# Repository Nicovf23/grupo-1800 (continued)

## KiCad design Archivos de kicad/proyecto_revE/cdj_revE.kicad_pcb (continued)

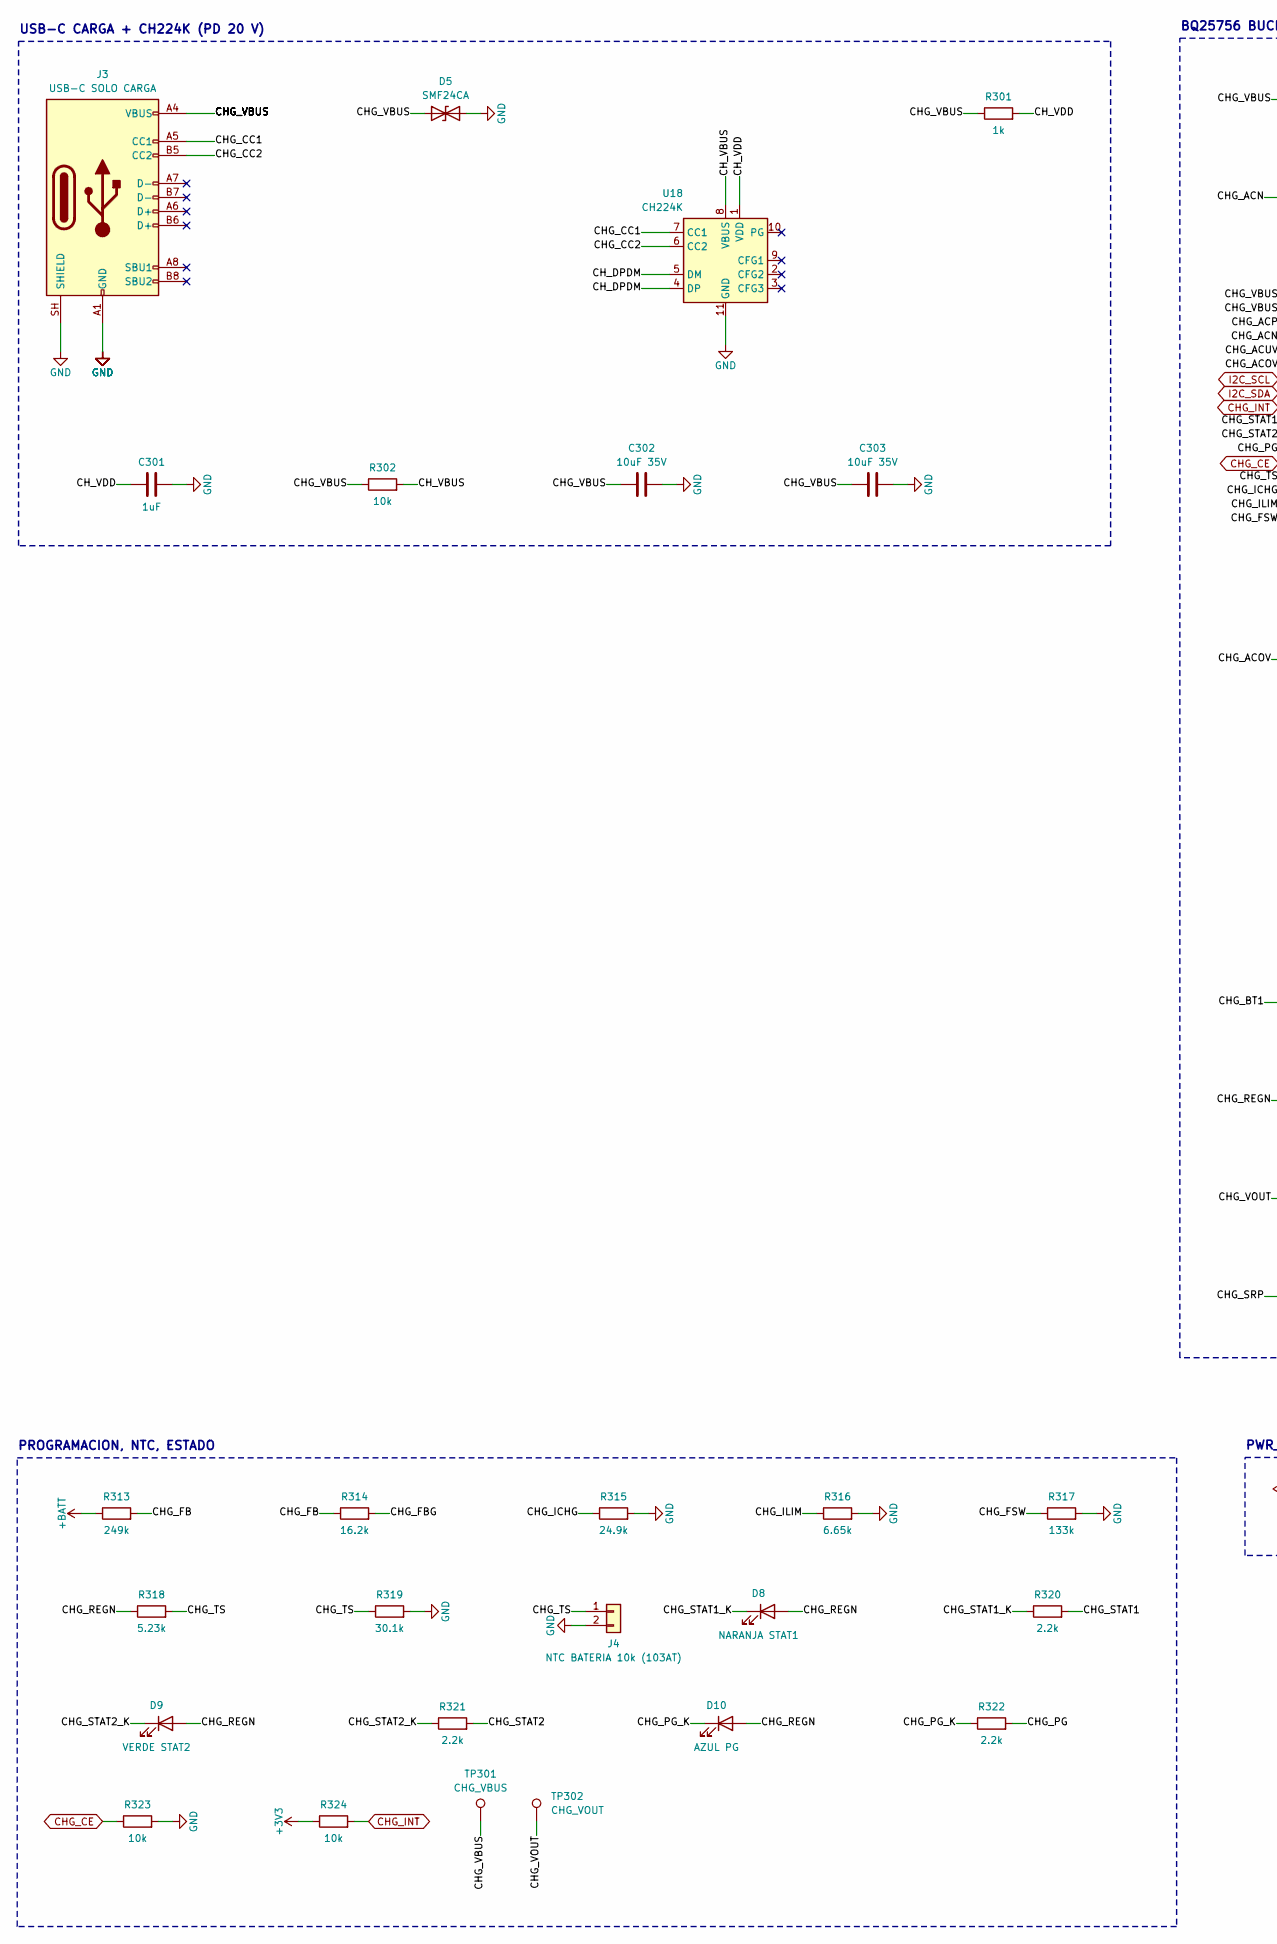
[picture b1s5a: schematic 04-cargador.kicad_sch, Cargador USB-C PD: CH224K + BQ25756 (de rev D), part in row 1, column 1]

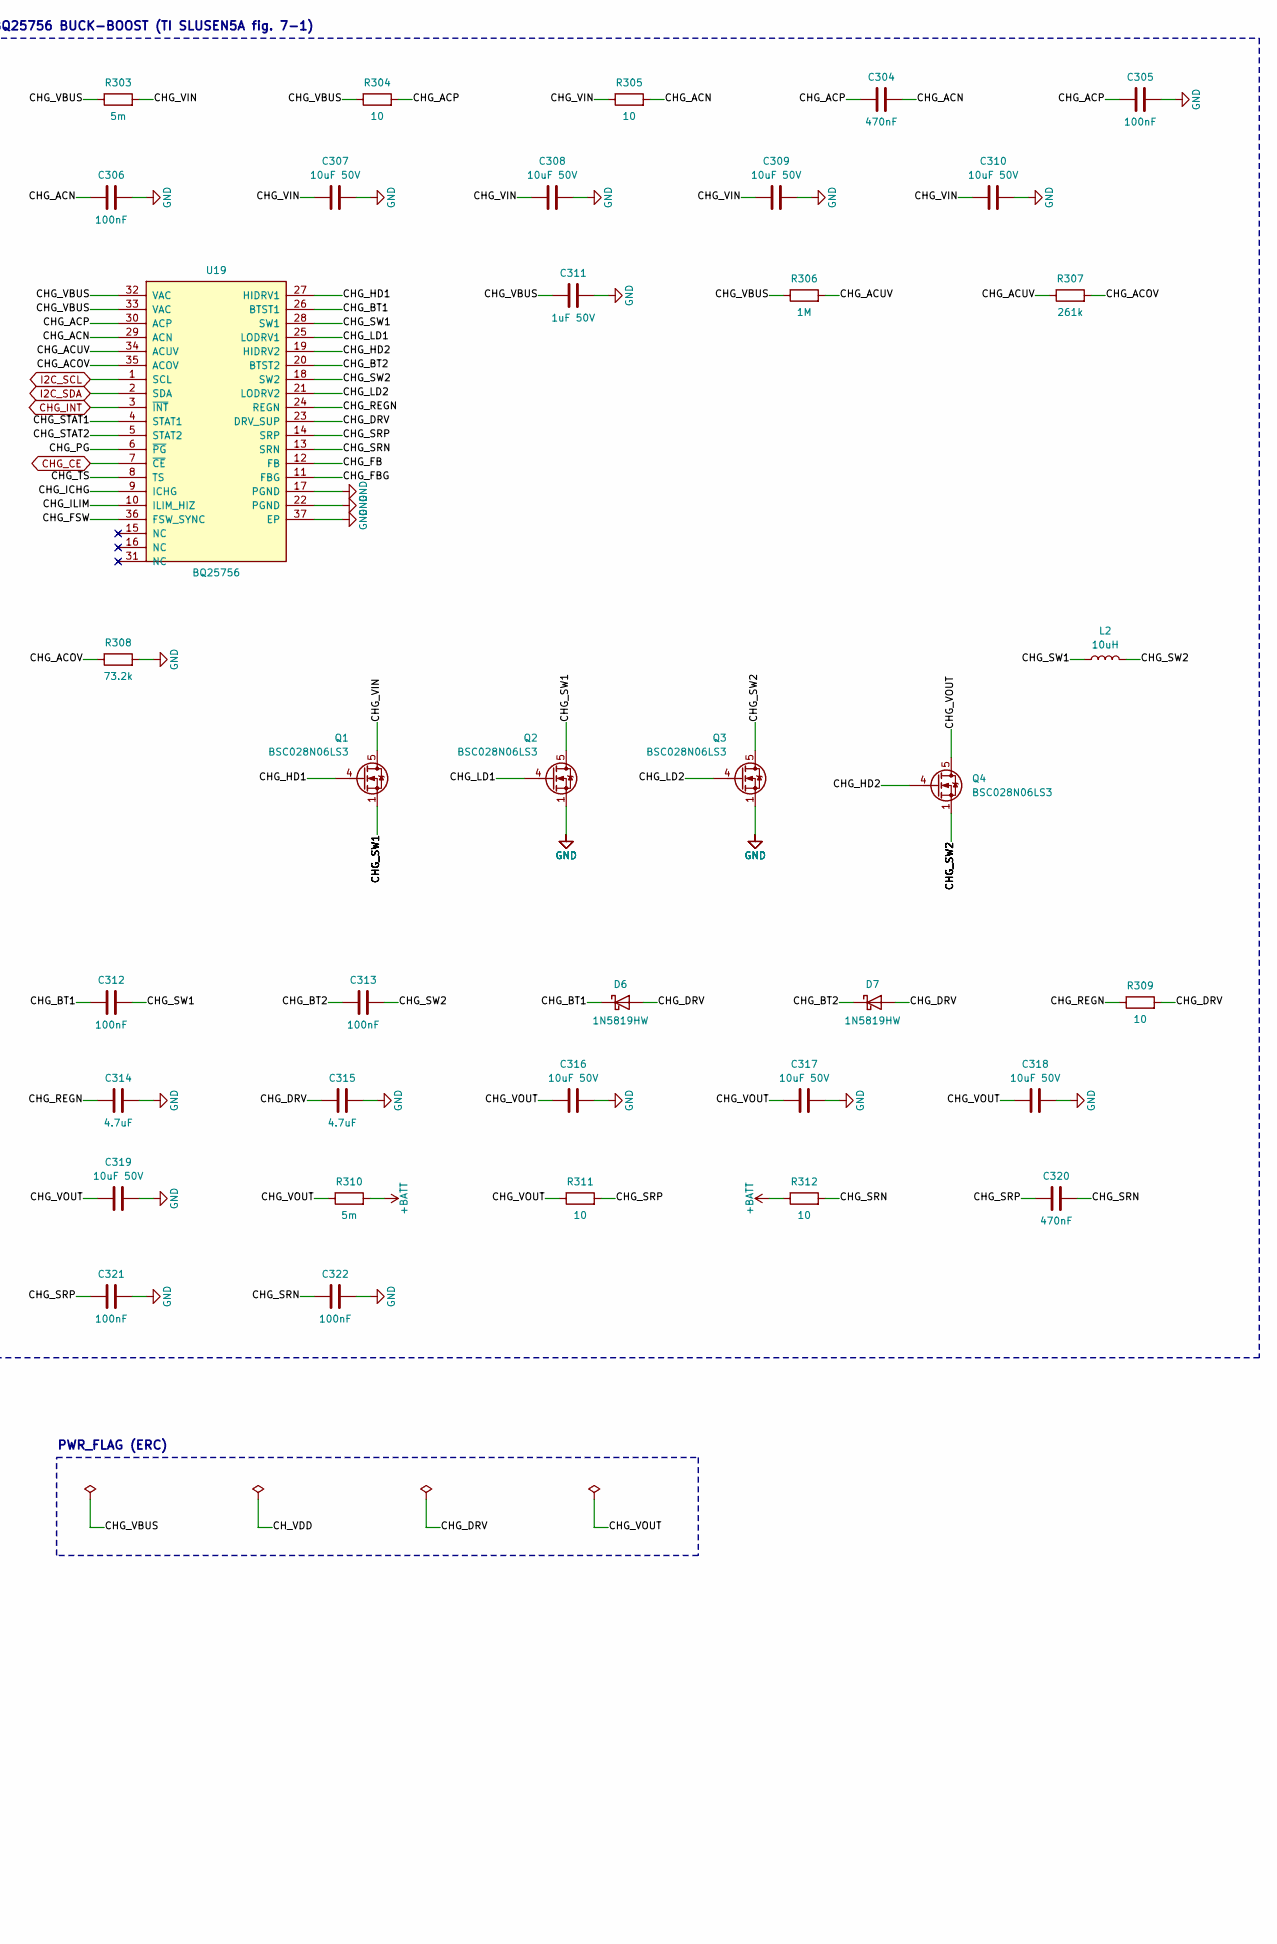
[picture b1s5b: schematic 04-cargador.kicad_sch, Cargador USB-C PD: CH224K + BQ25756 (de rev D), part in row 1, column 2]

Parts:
C301: 1uF; C_0603_1608Metric; MPN X7R 0603 25 V
C302, C303: 10uF 35V; C_1206_3216Metric; MPN X5R 1206 35 V
C304, C320: 470nF; C_0603_1608Metric; MPN X7R 0603 50 V
C305, C306, C321, C322: 100nF; C_0603_1608Metric; MPN X7R 0603 50 V
C307, C308, C309, C310, C316, C317, C318, C319: 10uF 50V; C_1206_3216Metric; MPN X5R 1206 50 V
C311: 1uF 50V; C_0603_1608Metric; MPN X7R 0603 50 V (VAC)
C312: 100nF; C_0603_1608Metric; MPN X7R 0603 25 V (bootstrap 1)
C313: 100nF; C_0603_1608Metric; MPN X7R 0603 25 V (bootstrap 2)
C314, C315: 4.7uF; C_0805_2012Metric; MPN X7R 0805 16 V
D5: SMF24CA; D_SOD-123F; MPN Littelfuse SMF24CA (profesor; PD 20 V <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
D6, D7: 1N5819HW; D_SOD-123; MPN Diodes 1N5819HW-7-F (profesor)
D8: NARANJA STAT1; LED_0603_1608Metric; MPN LED 0603
D9: VERDE STAT2; LED_0603_1608Metric; MPN LED 0603
D10: AZUL PG; LED_0603_1608Metric; MPN LED 0603
J3: USB-C SOLO CARGA; USB_C_Receptacle_HRO_TYPE-C-31-M-12; MPN HRO TYPE-C-31-M-12
J4: NTC BATERIA 10k (103AT); JST_PH_B2B-PH-K_1x02_P2.00mm_Vertical; MPN JST B2B-PH-K-S
L2: 10uH; L_Vishay_IHLP-4040; MPN Vishay IHLP4040DZER100M5A (10 uH, 6.5 A)
Q1, Q2, Q3, Q4: BSC028N06LS3; TDSON-8-1; MPN Infineon BSC028N06LS3 (60 V, 2.8 mOhm)
R301: 1k; R_0603_1608Metric; MPN 1 % 0603
R302, R324: 10k; R_0603_1608Metric; MPN 1 % 0603
R303: 5m; R_1206_3216Metric; MPN Shunt 5 mOhm 1206 1 W (RAC_SNS)
R304, R305, R309, R311, R312: 10; R_0603_1608Metric; MPN 1 % 0603
R306: 1M; R_0603_1608Metric; MPN 1 % 0603
R307: 261k; R_0603_1608Metric; MPN 1 % 0603
R308: 73.2k; R_0603_1608Metric; MPN 1 % 0603
R310: 5m; R_1206_3216Metric; MPN Shunt 5 mOhm 1206 1 W (RBAT_SNS)
R313: 249k; R_0603_1608Metric; MPN 1 % 0603 (FB: 25.14 V)
R314: 16.2k; R_0603_1608Metric; MPN 1 % 0603
R315: 24.9k; R_0603_1608Metric; MPN 1 % 0603 (ICHG 2.0 A)
R316: 6.65k; R_0603_1608Metric; MPN 1 % 0603 (ILIM 3.0 A)
R317: 133k; R_0603_1608Metric; MPN 1 % 0603 (250 kHz)
R318: 5.23k; R_0603_1608Metric; MPN 1 % 0603
R319: 30.1k; R_0603_1608Metric; MPN 1 % 0603
R320, R321, R322: 2.2k; R_0603_1608Metric; MPN 1 % 0603
R323: 10k; R_0603_1608Metric; MPN 1 % 0603 (carga habilitada sin ESP32)
TP301: CHG_VBUS; TestPoint_Pad_D1.5mm; MPN Pad de prueba
TP302: CHG_VOUT; TestPoint_Pad_D1.5mm; MPN Pad de prueba
U18: CH224K; SSOP-10-1EP_3.9x4.9mm_P1mm_EP2.1x3.3mm; MPN WCH CH224K
U19: BQ25756; QFN-36-1EP_5x6mm_P0.5mm_EP3.6x4.6mm; MPN TI BQ25756RRVR

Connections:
/Cargador USB-C PD: CH224K + BQ25756 (de rev D)/CHG_ACN: C304.2, C306.1, R305.2, U19.29 (ACN)
/Cargador USB-C PD: CH224K + BQ25756 (de rev D)/CHG_ACOV: R307.2, R308.1, U19.35 (ACOV)
/Cargador USB-C PD: CH224K + BQ25756 (de rev D)/CHG_ACP: C304.1, C305.1, R304.2, U19.30 (ACP)
/Cargador USB-C PD: CH224K + BQ25756 (de rev D)/CHG_ACUV: R306.2, R307.1, U19.34 (ACUV)
/Cargador USB-C PD: CH224K + BQ25756 (de rev D)/CHG_BT1: C312.1, D6.1 (K), U19.26 (BTST1)
/Cargador USB-C PD: CH224K + BQ25756 (de rev D)/CHG_BT2: C313.1, D7.1 (K), U19.20 (BTST2)
/Cargador USB-C PD: CH224K + BQ25756 (de rev D)/CHG_CC1: J3.A5 (CC1), U18.7 (CC1)
/Cargador USB-C PD: CH224K + BQ25756 (de rev D)/CHG_CC2: J3.B5 (CC2), U18.6 (CC2)
/Cargador USB-C PD: CH224K + BQ25756 (de rev D)/CHG_FB: R313.2, R314.1, U19.12 (FB)
/Cargador USB-C PD: CH224K + BQ25756 (de rev D)/CHG_FBG: R314.2, U19.11 (FBG)
/Cargador USB-C PD: CH224K + BQ25756 (de rev D)/CHG_FSW: R317.1, U19.36 (FSW_SYNC)
/Cargador USB-C PD: CH224K + BQ25756 (de rev D)/CHG_HD1: Q1.4 (G), U19.27 (HIDRV1)
/Cargador USB-C PD: CH224K + BQ25756 (de rev D)/CHG_HD2: Q4.4 (G), U19.19 (HIDRV2)
/Cargador USB-C PD: CH224K + BQ25756 (de rev D)/CHG_ICHG: R315.1, U19.9 (ICHG)
/Cargador USB-C PD: CH224K + BQ25756 (de rev D)/CHG_ILIM: R316.1, U19.10 (ILIM_HIZ)
/Cargador USB-C PD: CH224K + BQ25756 (de rev D)/CHG_LD1: Q2.4 (G), U19.25 (LODRV1)
/Cargador USB-C PD: CH224K + BQ25756 (de rev D)/CHG_LD2: Q3.4 (G), U19.21 (LODRV2)
/Cargador USB-C PD: CH224K + BQ25756 (de rev D)/CHG_PG: R322.2, U19.6 (~PG)
/Cargador USB-C PD: CH224K + BQ25756 (de rev D)/CHG_PG_K: D10.1 (K), R322.1
/Cargador USB-C PD: CH224K + BQ25756 (de rev D)/CHG_REGN: C314.1, D8.2 (A), D9.2 (A), D10.2 (A), R309.1, R318.1, U19.24 (REGN)
/Cargador USB-C PD: CH224K + BQ25756 (de rev D)/CHG_SRN: C320.2, C322.1, R312.2, U19.13 (SRN)
/Cargador USB-C PD: CH224K + BQ25756 (de rev D)/CHG_SRP: C320.1, C321.1, R311.2, U19.14 (SRP)
/Cargador USB-C PD: CH224K + BQ25756 (de rev D)/CHG_STAT1: R320.2, U19.4 (STAT1)
/Cargador USB-C PD: CH224K + BQ25756 (de rev D)/CHG_STAT1_K: D8.1 (K), R320.1
/Cargador USB-C PD: CH224K + BQ25756 (de rev D)/CHG_STAT2: R321.2, U19.5 (STAT2)
/Cargador USB-C PD: CH224K + BQ25756 (de rev D)/CHG_STAT2_K: D9.1 (K), R321.1
/Cargador USB-C PD: CH224K + BQ25756 (de rev D)/CHG_SW1: C312.2, L2.1, Q1.1 (S), Q1.2 (S), Q1.3 (S), Q2.5 (D), U19.28 (SW1)
/Cargador USB-C PD: CH224K + BQ25756 (de rev D)/CHG_SW2: C313.2, L2.2, Q3.5 (D), Q4.1 (S), Q4.2 (S), Q4.3 (S), U19.18 (SW2)
/Cargador USB-C PD: CH224K + BQ25756 (de rev D)/CHG_TS: J4.1, R318.2, R319.1, U19.8 (TS)
/Cargador USB-C PD: CH224K + BQ25756 (de rev D)/CHG_VIN: C307.1, C308.1, C309.1, C310.1, Q1.5 (D), R303.2, R305.1
/Cargador USB-C PD: CH224K + BQ25756 (de rev D)/CH_DPDM: U18.4 (DP), U18.5 (DM)
/Cargador USB-C PD: CH224K + BQ25756 (de rev D)/CH_VBUS: R302.2, U18.8 (VBUS)
CHG_CE: R323.1, U19.7 (~CE); also elsewhere on the board
CHG_INT: R324.2, U19.3 (~INT); also elsewhere on the board
I2C_SCL: U19.1 (SCL); also elsewhere on the board
I2C_SDA: U19.2 (SDA); also elsewhere on the board

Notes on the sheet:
USB-C CARGA + CH224K (PD 20 V)
PROGRAMACION, NTC, ESTADO
BQ25756 BUCK-BOOST (TI SLUSEN5A fig. 7-1)
PWR_FLAG (ERC)

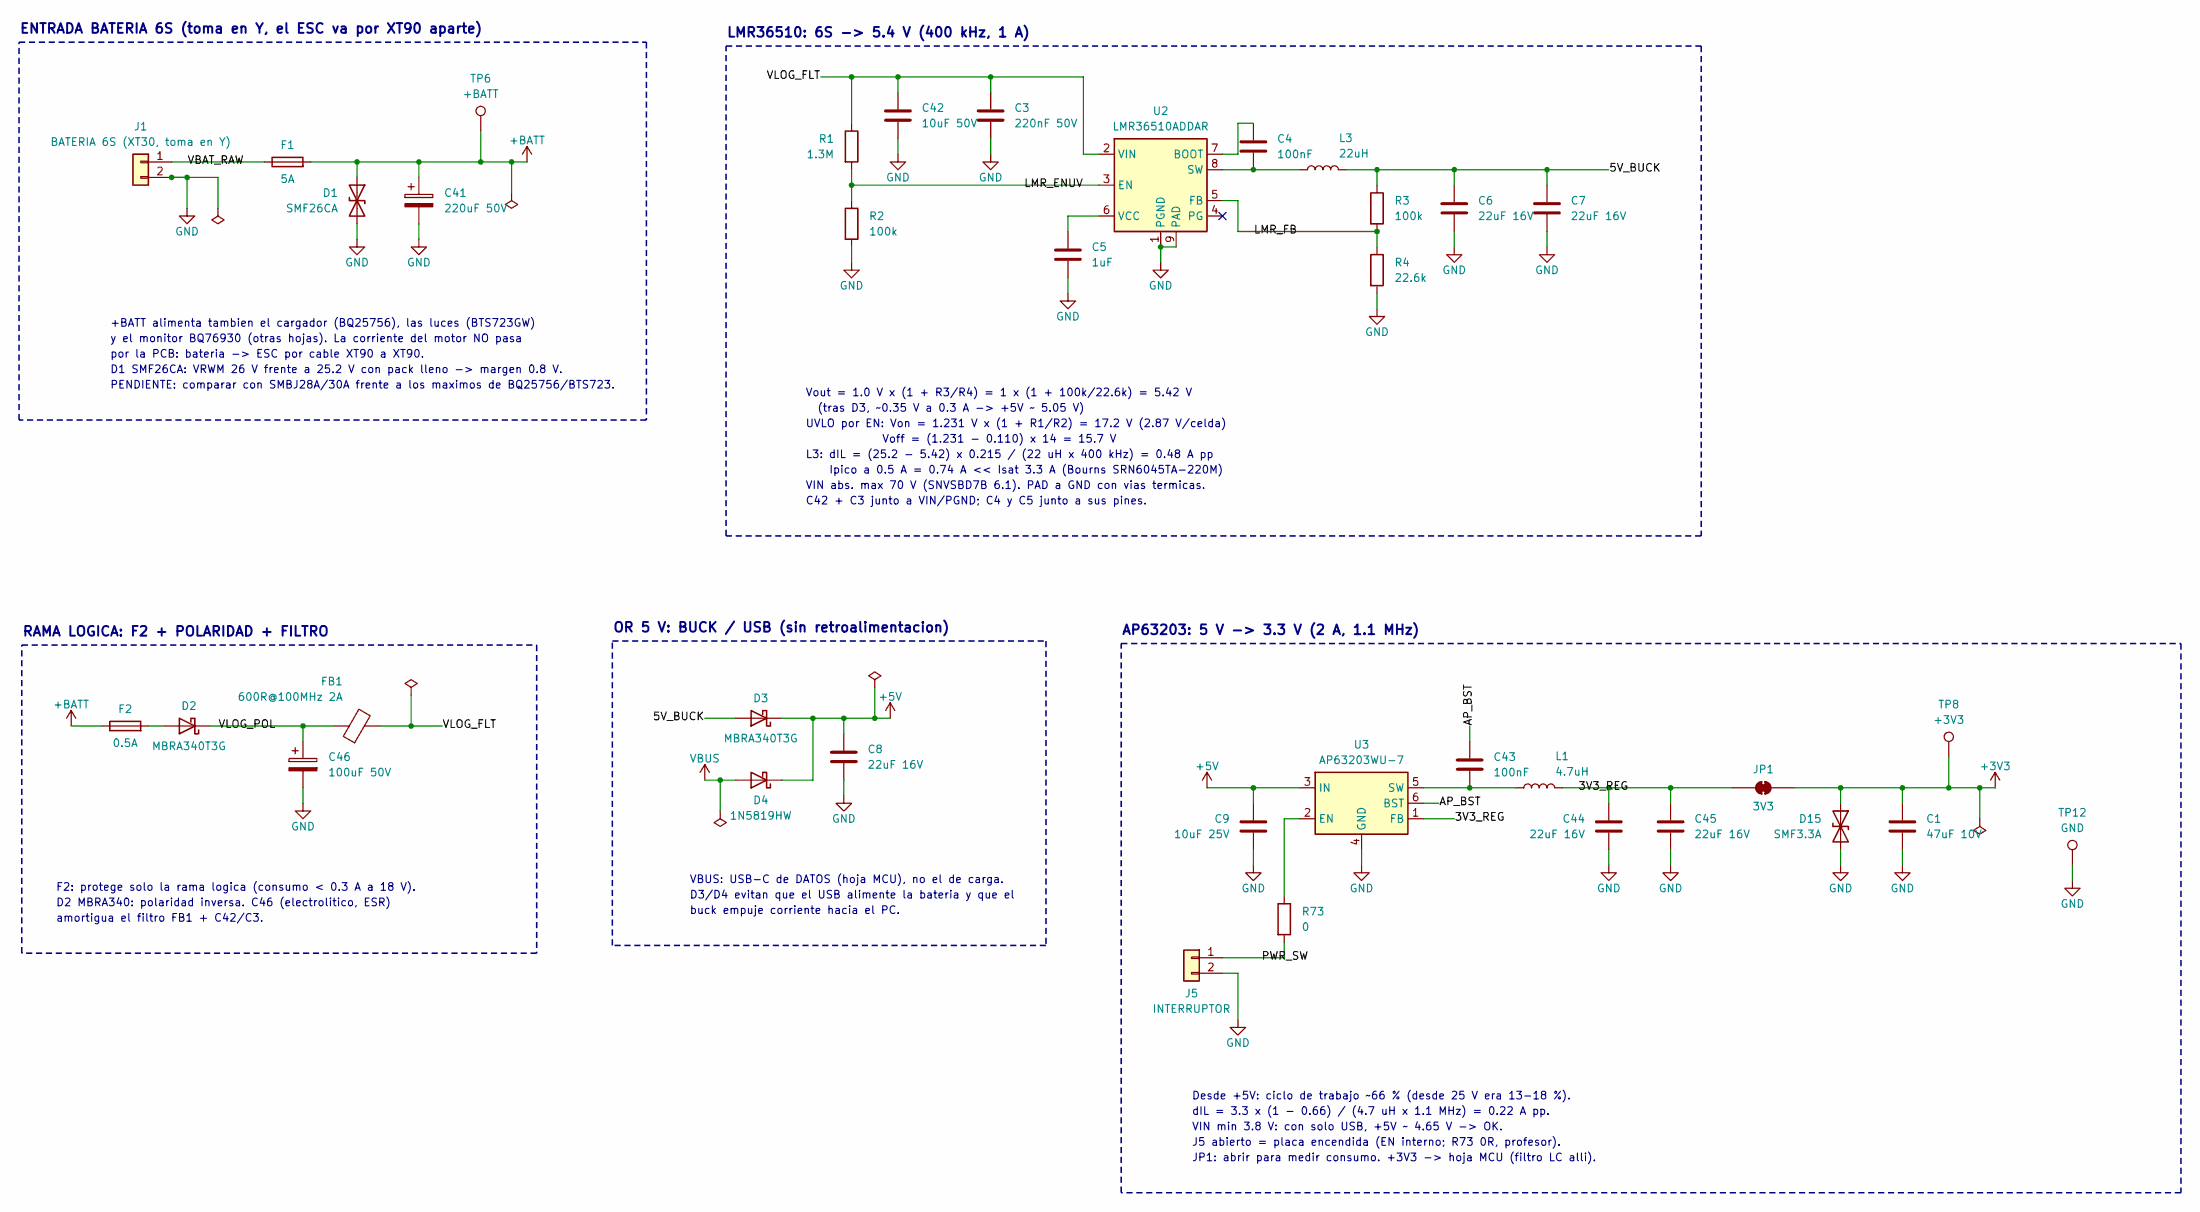
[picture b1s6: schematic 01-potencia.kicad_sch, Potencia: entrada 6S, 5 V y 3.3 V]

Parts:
C1: 47uF 10V; C_1206_3216Metric; MPN X5R 1206 10 V (profesor)
C3: 220nF 50V; C_0603_1608Metric; MPN X7R 0603 50 V (CIN HF, tabla 8-1)
C4: 100nF; C_0603_1608Metric; MPN X7R 0603 16 V (BOOT, tabla 5-1)
C5: 1uF; C_0603_1608Metric; MPN X7R 0603 16 V (VCC, tabla 5-1)
C6, C7, C8: 22uF 16V; C_1206_3216Metric; MPN X5R/X7R 1206 16 V
C9: 10uF 25V; C_1206_3216Metric; MPN X5R/X7R 1206 25 V (C1 tabla 2)
C41: 220uF 50V; CP_Elec_10x10.5; MPN Aluminio 220 uF / 50 V (profesor)
C42: 10uF 50V; C_1206_3216Metric; MPN X7R/X5R 1206 50 V (profesor; CIN >= 2.2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
C43: 100nF; C_0603_1608Metric; MPN X7R 0603 25 V (C3 tabla 2, profesor)
C44, C45: 22uF 16V; C_1206_3216Metric; MPN X5R 1206 16 V (C2 tabla 2, profesor)
C46: 100uF 50V; CP_Elec_8x10.5; MPN Aluminio 100 uF / 50 V (profesor)
D1: SMF26CA; D_SOD-123F; MPN Littelfuse SMF26CA
D2, D3: MBRA340T3G; D_SMA; MPN onsemi MBRA340T3G (profesor)
D4: 1N5819HW; D_SOD-123; MPN Diodes 1N5819HW-7-F (profesor)
D15: SMF3.3A; D_SOD-123F; MPN SMF3.3A (profesor; verificar fabricante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
F1: 5A; Fuse_Littelfuse-NANO2-451_453; MPN Littelfuse 0451005.MRL (verificar Vr >=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
F2: 0.5A; Fuse_1206_3216Metric; MPN A definir en el bloque 8 (BOM): >= 63 V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
FB1: 600R@100MHz 2A; L_1206_3216Metric; MPN A definir en el bloque 8 (BOM): ferrita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
J1: BATERIA 6S (XT30, toma en Y); AMASS_XT30PW-M_1x02_P2.50mm_Horizontal; MPN AMASS XT30PW-M
J5: INTERRUPTOR; JST_PH_B2B-PH-K_1x02_P2.00mm_Vertical; MPN JST B2B-PH-K-S
JP1: 3V3; SolderJumper-2_P1.3mm_Bridged_RoundedPad1.0x1.5mm; MPN Puente de soldadura (profesor)
L1: 4.7uH; L_APV_APH0630; MPN APV APH0630T4R7M (profesor)
L3: 22uH; L_Bourns_SRN6045TA; MPN Bourns SRN6045TA-220M (22 uH, Isat 3.3 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
R1: 1.3M; R_0603_1608Metric; MPN 1 % 0603
R2: 100k; R_0603_1608Metric; MPN 1 % 0603
R3: 100k; R_0603_1608Metric; MPN 1 % 0603 (RFBT)
R4: 22.6k; R_0603_1608Metric; MPN 1 % 0603 (RFBB -> 5.42 V)
R73: 0; R_0603_1608Metric; MPN 0 R 0603 (profesor)
TP6: +BATT; TestPoint_Pad_D1.5mm
TP8: +3V3; TestPoint_Pad_D1.5mm
TP12: GND; TestPoint_Pad_D1.5mm
U2: LMR36510ADDAR; Texas_HTSOP-8-1EP_3.9x4.9mm_P1.27mm_EP2.95x4.9mm_Mask2.4x3.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; MPN TI LMR36510ADDAR (65 V, 1 A, 400 kHz, P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
U3: AP63203WU-7; TSOT-23-6; MPN Diodes AP63203WU-7 (profesor)

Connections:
/Potencia: entrada 6S, 5 V y 3.3 V/3V3_REG: C44.1, C45.1, JP1.1 (A), L1.2, U3.1 (FB)
/Potencia: entrada 6S, 5 V y 3.3 V/5V_BUCK: C6.1, C7.1, D3.2 (A), L3.2, R3.1
/Potencia: entrada 6S, 5 V y 3.3 V/AP_BST: C43.1, U3.6 (BST)
/Potencia: entrada 6S, 5 V y 3.3 V/LMR_ENUV: R1.2, R2.1, U2.3 (EN)
/Potencia: entrada 6S, 5 V y 3.3 V/LMR_FB: R3.2, R4.1, U2.5 (FB)
/Potencia: entrada 6S, 5 V y 3.3 V/PWR_SW: J5.1, R73.2
/Potencia: entrada 6S, 5 V y 3.3 V/VBAT_RAW: F1.1, J1.1
/Potencia: entrada 6S, 5 V y 3.3 V/VLOG_POL: C46.1, D2.1 (K), FB1.1
unnamed: D2.2 (A), F2.2
unnamed: C4.1, U2.7 (BOOT)
unnamed: C4.2, L3.1, U2.8 (SW)
unnamed: C5.1, U2.6 (VCC)
unnamed: R73.1, U3.2 (EN)
unnamed: C43.2, L1.1, U3.5 (SW)

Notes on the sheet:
+BATT alimenta tambien el cargador (BQ25756), las luces (BTS723GW)
LMR36510: 6S -> 5.4 V (400 kHz, 1 A)
F2: protege solo la rama logica (consumo < 0.3 A a 18 V).
L3: dIL = (25.2 - 5.42) x 0.215 / (22 uH x 400 kHz) = 0.48 A pp
C42 + C3 junto a VIN/PGND; C4 y C5 junto a sus pines.
J5 abierto = placa encendida (EN interno; R73 0R, profesor).
OR 5 V: BUCK / USB (sin retroalimentacion)
RAMA LOGICA: F2 + POLARIDAD + FILTRO
PENDIENTE: comparar con SMBJ28A/30A frente a los maximos de BQ25756/BTS723.
por la PCB: bateria -> ESC por cable XT90 a XT90.
y el monitor BQ76930 (otras hojas). La corriente del motor NO pasa
(tras D3, ~0.35 V a 0.3 A -> +5V ~ 5.05 V)
VIN min 3.8 V: con solo USB, +5V ~ 4.65 V -> OK.
Voff = (1.231 - 0.110) x 14 = 15.7 V
dIL = 3.3 x (1 - 0.66) / (4.7 uH x 1.1 MHz) = 0.22 A pp.
JP1: abrir para medir consumo. +3V3 -> hoja MCU (filtro LC alli).
D1 SMF26CA: VRWM 26 V frente a 25.2 V con pack lleno -> margen 0.8 V.
amortigua el filtro FB1 + C42/C3.
Vout = 1.0 V x (1 + R3/R4) = 1 x (1 + 100k/22.6k) = 5.42 V
VIN abs. max 70 V (SNVSBD7B 6.1). PAD a GND con vias termicas.
UVLO por EN: Von = 1.231 V x (1 + R1/R2) = 17.2 V (2.87 V/celda)
D2 MBRA340: polaridad inversa. C46 (electrolitico, ESR)
buck empuje corriente hacia el PC.
ENTRADA BATERIA 6S (toma en Y, el ESC va por XT90 aparte)
VBUS: USB-C de DATOS (hoja MCU), no el de carga.
Ipico a 0.5 A = 0.74 A << Isat 3.3 A (Bourns SRN6045TA-220M)
D3/D4 evitan que el USB alimente la bateria y que el
AP63203: 5 V -> 3.3 V (2 A, 1.1 MHz)
Desde +5V: ciclo de trabajo ~66 % (desde 25 V era 13-18 %).

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
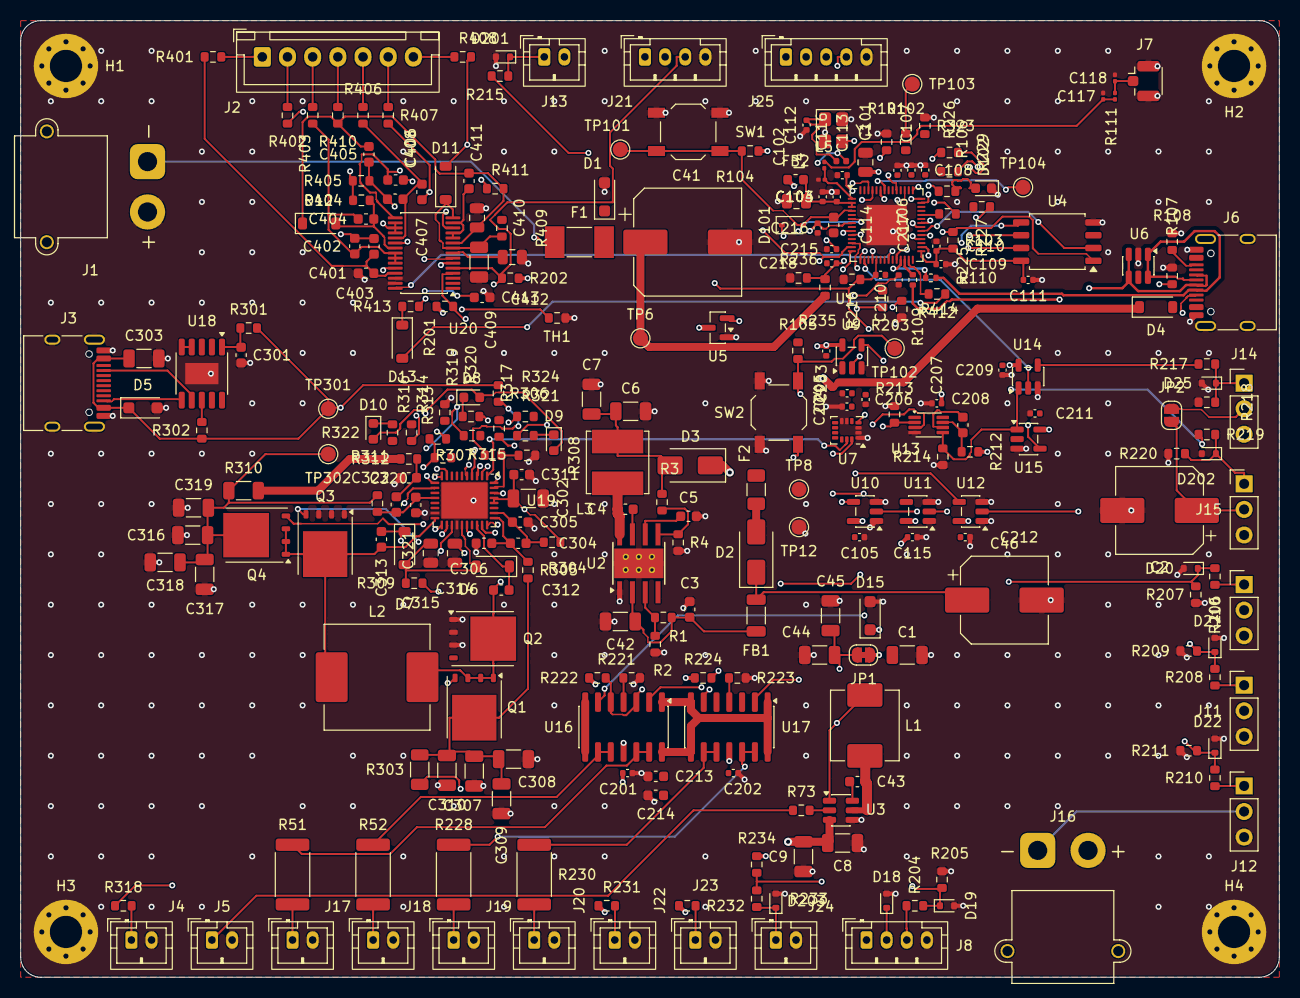
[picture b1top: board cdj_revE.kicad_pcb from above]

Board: 4 copper layers, 125.0 x 95.0 mm, 278 parts (0 on the bottom side), 172 nets.

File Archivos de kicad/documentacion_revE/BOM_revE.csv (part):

Referencias,Cantidad,Valor,Huella,MPN / especificacion,Estado
C1,1,47uF 10V,C_1206_3216Metric,X5R 1206 10 V (profesor),MPN indicado (stock sin comprobar)
C2,1,470uF 16V,CP_Elec_8x10.5,Aluminio 470 uF / 16 V (profesor),MPN indicado (stock sin comprobar)
C3,1,220nF 50V,C_0603_1608Metric,"X7R 0603 50 V (CIN HF, tabla 8-1)",MPN indicado (stock sin comprobar)
C4,1,100nF,C_0603_1608Metric,"X7R 0603 16 V (BOOT, tabla 5-1)",MPN indicado (stock sin comprobar)
C5,1,1uF,C_0603_1608Metric,"X7R 0603 16 V (VCC, tabla 5-1)",MPN indicado (stock sin comprobar)
C6 C7 C8,3,22uF 16V,C_1206_3216Metric,X5R/X7R 1206 16 V,MPN indicado (stock sin comprobar)
C9,1,10uF 25V,C_1206_3216Metric,X5R/X7R 1206 25 V (C1 tabla 2),MPN indicado (stock sin comprobar)
C41,1,220uF 50V,CP_Elec_10x10.5,Aluminio 220 uF / 50 V (profesor),MPN indicado (stock sin comprobar)
C42,1,10uF 50V,C_1206_3216Metric,X7R/X5R 1206 50 V (profesor; CIN >= 2.2 uF efectivos),MPN indicado (stock sin comprobar)
C43,1,100nF,C_0603_1608Metric,"X7R 0603 25 V (C3 tabla 2, profesor)",MPN indicado (stock sin comprobar)
C44 C45,2,22uF 16V,C_1206_3216Metric,"X5R 1206 16 V (C2 tabla 2, profesor)",MPN indicado (stock sin comprobar)
C46,1,100uF 50V,CP_Elec_8x10.5,Aluminio 100 uF / 50 V (profesor),MPN indicado (stock sin comprobar)
C101,1,10uF,C_0805_2012Metric,"X5R 0805 10 V (entrada >= 10 uF, guía)",MPN indicado (stock sin comprobar)
C102,1,10uF,C_0805_2012Metric,X5R 0805 10 V (VDD3P3 pines 2/3),MPN indicado (stock sin comprobar)
C103 C203,2,1uF,C_0402_1005Metric,X5R 0402,MPN indicado (stock sin comprobar)
C104 C201 C202 C204 C205 C206 C207 C209 C211 C212 C215 C216 C217 C218,14,100nF,C_0402_1005Metric,X7R 0402,MPN indicado (stock sin comprobar)
C105,1,100nF,C_0402_1005Metric,X7R 0402 (VDD3P3_RTC pin 20),MPN indicado (stock sin comprobar)
C106,1,100nF,C_0402_1005Metric,X7R 0402 (VDD3P3_CPU pin 46),MPN indicado (stock sin comprobar)
C107,1,1uF,C_0402_1005Metric,X5R 0402 (VDDA pines 55/56),MPN indicado (stock sin comprobar)
C108,1,100nF,C_0402_1005Metric,X7R 0402 (VDDA pines 55/56),MPN indicado (stock sin comprobar)
C109,1,1uF,C_0402_1005Metric,"X5R 0402 (VDD_SPI, guía: 0.1 + 1 uF)",MPN indicado (stock sin comprobar)
C110,1,100nF,C_0402_1005Metric,X7R 0402 (VDD_SPI),MPN indicado (stock sin comprobar)
C111,1,100nF,C_0402_1005Metric,X7R 0402 (junto a U4 pin 8),MPN indicado (stock sin comprobar)
C112,1,15pF,C_0402_1005Metric,C0G 0402 (CL=10 pF: 2x(CL-Cstray); ajustar con prueba TX),MPN indicado (stock sin comprobar)
C113,1,15pF,C_0402_1005Metric,C0G 0402 (ajustar con prueba TX),MPN indicado (stock sin comprobar)
C114,1,1uF,C_0603_1608Metric,X5R 0603,MPN indicado (stock sin comprobar)
C115,1,100nF,C_0402_1005Metric,X7R 0402 (VDD supervisor),MPN indicado (stock sin comprobar)
C116,1,1.5pF,C_0201_0603Metric,"C0G 0201 (C11 1.2-1.8 pF, guía; ajustar con VNA)",MPN indicado (stock sin comprobar)
C117,1,1.5pF,C_0201_0603Metric,"C0G 0201 (C12 1.2-1.8 pF, guía)",MPN indicado (stock sin comprobar)
C118,1,DNP,C_0201_0603Metric,Sin montar (adaptación lado antena),MPN indicado (stock sin comprobar)
C208,1,470nF,C_0603_1608Metric,X7R 0603 (Cext; + en Rext/Cext),MPN indicado (stock sin comprobar)
C210,1,100nF,C_0402_1005Metric,X7R 0402 (antirrebote),MPN indicado (stock sin comprobar)
C213 C214,2,100nF 50V,C_0603_1608Metric,X7R 0603 50 V,MPN indicado (stock sin comprobar)
C301 C411,2,1uF,C_0603_1608Metric,X7R 0603 25 V,MPN indicado (stock sin comprobar)
C302 C303,2,10uF 35V,C_1206_3216Metric,X5R 1206 35 V,MPN indicado (stock sin comprobar)
C304 C320,2,470nF,C_0603_1608Metric,X7R 0603 50 V,MPN indicado (stock sin comprobar)
C305 C306 C321 C322,4,100nF,C_0603_1608Metric,X7R 0603 50 V,MPN indicado (stock sin comprobar)
C307 C308 C309 C310 C316 C317 C318 C319,8,10uF 50V,C_1206_3216Metric,X5R 1206 50 V,MPN indicado (stock sin comprobar)
C311,1,1uF 50V,C_0603_1608Metric,X7R 0603 50 V (VAC),MPN indicado (stock sin comprobar)
C312,1,100nF,C_0603_1608Metric,X7R 0603 25 V (bootstrap 1),MPN indicado (stock sin comprobar)
C313,1,100nF,C_0603_1608Metric,X7R 0603 25 V (bootstrap 2),MPN indicado (stock sin comprobar)
C314 C315,2,4.7uF,C_0805_2012Metric,X7R 0805 16 V,MPN indicado (stock sin comprobar)
C401 C402 C403 C404 C405 C406 C407 C408,8,1uF,C_0603_1608Metric,X7R 0603 25 V (Cc filtro celda),MPN indicado (stock sin comprobar)
C409,1,10uF 50V,C_1206_3216Metric,X7R 1206 50 V (Cf BAT),MPN indicado (stock sin comprobar)
C410,1,10uF 25V,C_0805_2012Metric,X7R 0805 25 V,MPN indicado (stock sin comprobar)
C412,1,4.7uF,C_0805_2012Metric,X7R 0805 10 V,MPN indicado (stock sin comprobar)
C413,1,1uF,C_0603_1608Metric,X7R 0603,MPN indicado (stock sin comprobar)
D1,1,SMF26CA,D_SOD-123F,Littelfuse SMF26CA,MPN indicado (stock sin comprobar)
D2 D3,2,MBRA340T3G,D_SMA,onsemi MBRA340T3G (profesor),MPN indicado (stock sin comprobar)
D4 D6 D7 D13,4,1N5819HW,D_SOD-123,Diodes 1N5819HW-7-F (profesor),MPN indicado (stock sin comprobar)
D5,1,SMF24CA,D_SOD-123F,Littelfuse SMF24CA (profesor; PD 20 V < 24 V VRWM),MPN indicado (stock sin comprobar)
D8,1,NARANJA STAT1,LED_0603_1608Metric,LED 0603,MPN indicado (stock sin comprobar)
D9,1,VERDE STAT2,LED_0603_1608Metric,LED 0603,MPN indicado (stock sin comprobar)
D10,1,AZUL PG,LED_0603_1608Metric,LED 0603,MPN indicado (stock sin comprobar)
D11 D12,2,1N4148W,D_SOD-123,Diodes 1N4148W-7-F,MPN indicado (stock sin comprobar)
D15,1,SMF3.3A,D_SOD-123F,SMF3.3A (profesor; verificar fabricante/sufijo),PENDIENTE: elegir MPN
D18 D19 D20 D21 D22 D25 D201 D202 D203,9,ESD5Z3.3T,D_SOD-523,onsemi ESD5Z3.3T1G (profesor),MPN indicado (stock sin comprobar)
D101,1,BAT54WS,D_SOD-323,BAT54WS (solo tira CHIP_PU hacia abajo),MPN indicado (stock sin comprobar)
D102,1,AZUL ESTADO,LED_0603_1608Metric,LED 0603,MPN indicado (stock sin comprobar)
F1,1,5A,Fuse_Littelfuse-NANO2-451_453,Littelfuse 0451005.MRL (verificar Vr >= 32 V),PENDIENTE: elegir MPN
F2,1,0.5A,Fuse_1206_3216Metric,"A definir en el bloque 8 (BOM): >= 63 V, retardo, 1206",PENDIENTE: elegir MPN
FB1,1,600R@100MHz 2A,L_1206_3216Metric,A definir en el bloque 8 (BOM): ferrita 1206 >= 1 A,PENDIENTE: elegir MPN
FB2,1,120R@100MHz 2A,L_0603_1608Metric,A definir en BOM: ferrita 0603 >= 500 mA,PENDIENTE: elegir MPN
J1,1,"BATERIA 6S (XT30, toma en Y)",AMASS_XT30PW-M_1x02_P2.50mm_Horizontal,AMASS XT30PW-M,MPN indicado (stock sin comprobar)
J2,1,BALANCEO 6S (JST-XH),JST_XH_B7B-XH-A_1x07_P2.50mm_Vertical,JST B7B-XH-A,MPN indicado (stock sin comprobar)
J3,1,USB-C SOLO CARGA,USB_C_Receptacle_HRO_TYPE-C-31-M-12,HRO TYPE-C-31-M-12,MPN indicado (stock sin comprobar)
J4,1,NTC BATERIA 10k (103AT),JST_PH_B2B-PH-K_1x02_P2.00mm_Vertical,JST B2B-PH-K-S,MPN indicado (stock sin comprobar)
J5,1,INTERRUPTOR,JST_PH_B2B-PH-K_1x02_P2.00mm_Vertical,JST B2B-PH-K-S,MPN indicado (stock sin comprobar)
J6,1,USB-C DATOS,USB_C_Receptacle_HRO_TYPE-C-31-M-12,HRO TYPE-C-31-M-12,MPN indicado (stock sin comprobar)
J7,1,U.FL,U.FL_Hirose_U.FL-R-SMT-1_Vertical,Hirose U.FL-R-SMT-1(10),MPN indicado (stock sin comprobar)
J8,1,RX SERIE (CRSF/ELRS),JST_PH_B4B-PH-K_1x04_P2.00mm_Vertical,JST B4B-PH-K-S,MPN indicado (stock sin comprobar)
J10,1,RC_CH1 PWM,PinHeader_1x03_P2.54mm_Vertical,Header 1x03 2.54 mm,MPN indicado (stock sin comprobar)
J11,1,RC_CH2 PWM,PinHeader_1x03_P2.54mm_Vertical,Header 1x03 2.54 mm,MPN indicado (stock sin comprobar)
J12,1,RC_CH3 PWM,PinHeader_1x03_P2.54mm_Vertical,Header 1x03 2.54 mm,MPN indicado (stock sin comprobar)
J13,1,INTERRUPTOR ARMADO,JST_PH_B2B-PH-K_1x02_P2.00mm_Vertical,JST B2B-PH-K-S,MPN indicado (stock sin comprobar)
J14,1,ESC,PinHeader_1x03_P2.54mm_Vertical,Header 1x03 2.54 mm,MPN indicado (stock sin comprobar)
J15,1,SERVO,PinHeader_1x03_P2.54mm_Vertical,Header 1x03 2.54 mm,MPN indicado (stock sin comprobar)
J16,1,VSERVO IN (BEC),AMASS_XT30PW-M_1x02_P2.50mm_Horizontal,AMASS XT30PW-M,MPN indicado (stock sin comprobar)
J17,1,LUZ blancas delanteras,JST_PH_B2B-PH-K_1x02_P2.00mm_Vertical,JST B2B-PH-K-S,MPN indicado (stock sin comprobar)
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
